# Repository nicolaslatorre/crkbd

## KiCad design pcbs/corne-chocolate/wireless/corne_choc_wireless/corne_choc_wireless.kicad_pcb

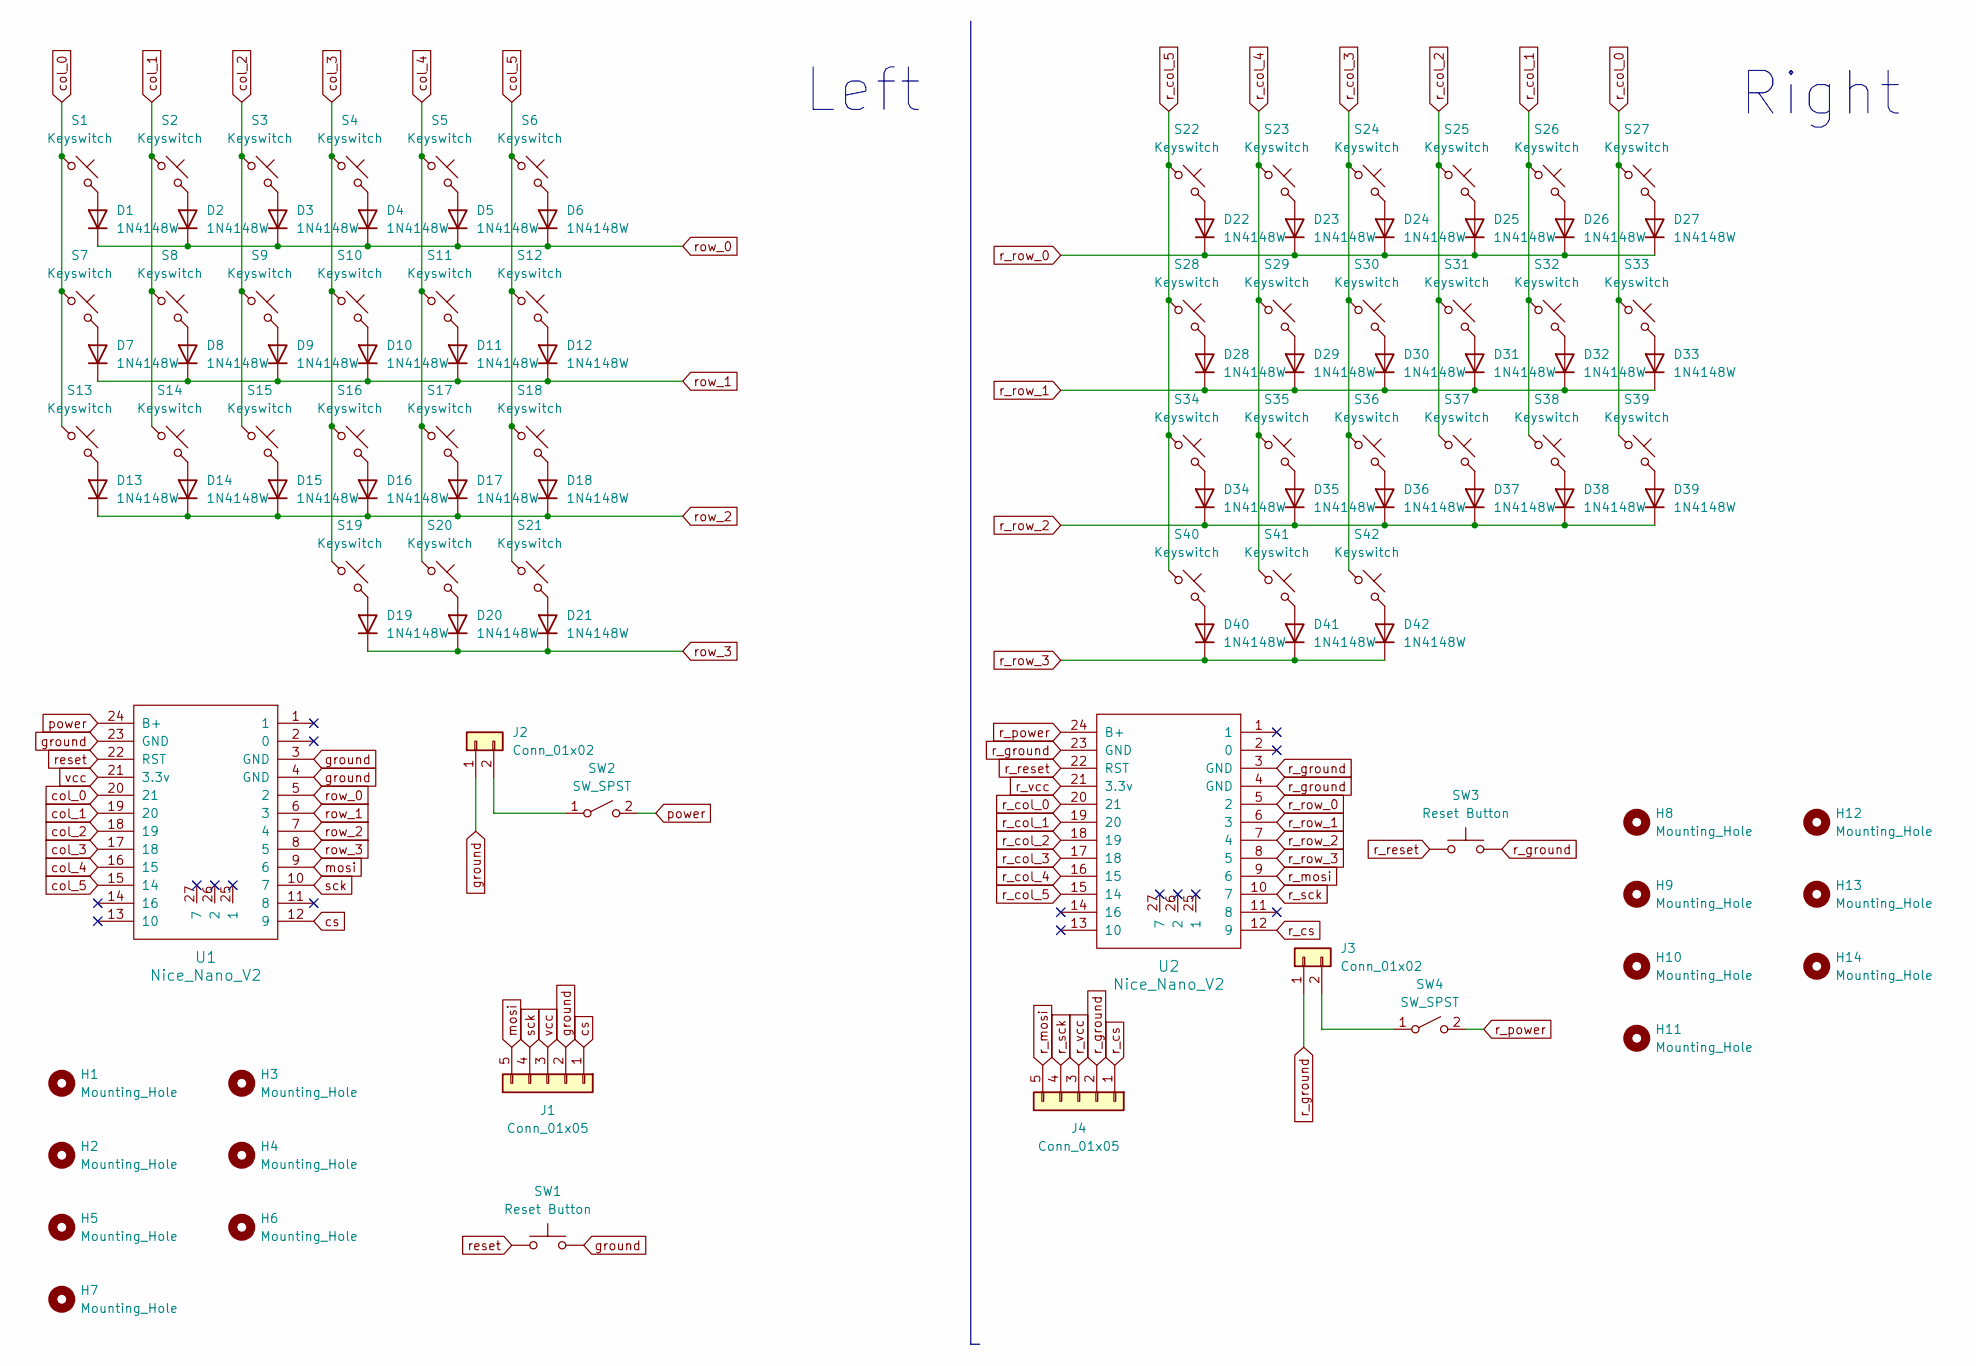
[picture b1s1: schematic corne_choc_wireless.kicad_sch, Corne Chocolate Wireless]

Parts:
D1, D2, D3, D4, D5, D6, D7, D8, D9, D10, D11, D12, D13, D14, D15, D16, D17, D18, D19, D20, D21, D22, D23, D24, D25, D26, D27, D28, D29, D30, D31, D32, D33, D34, D35, D36, D37, D38, D39, D40, D41, D42: 1N4148W; D_SOD-123
H1, H2, H3, H4, H5, H6, H7, H8, H9, H10, H11, H12, H13, H14: Mounting_Hole; MountingHole_2.2mm_M2_Pad
J1, J4: Conn_01x05; PinHeader_1x05_P2.54mm_Vertical
J2, J3: Conn_01x02; JST_PH_S2B-PH-K_1x02_P2.00mm_Horizontal
S1, S2, S3, S4, S5, S6, S7, S8, S9, S10, S11, S12, S13, S14, S15, S16, S17, S18, S19, S20, S22, S23, S24, S25, S26, S27, S28, S29, S30, S31, S32, S33, S34, S35, S36, S37, S38, S39, S41, S42: Keyswitch; Hotswap_Choc_V1_1.00u
S21, S40: Keyswitch; Hotswap_Choc_V1_1.50u
SW1, SW3: Reset Button; Button_MJTP1243
SW2, SW4: SW_SPST; Switch_MSK12C02
U1, U2: Nice_Nano_V2

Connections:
unnamed: D1.2 (A), S1.2
unnamed: D2.2 (A), S2.2
unnamed: D3.2 (A), S3.2
unnamed: D4.2 (A), S4.2
unnamed: D5.2 (A), S5.2
unnamed: D6.2 (A), S6.2
unnamed: D7.2 (A), S7.2
unnamed: D8.2 (A), S8.2
unnamed: D9.2 (A), S9.2
unnamed: D10.2 (A), S10.2
unnamed: D11.2 (A), S11.2
unnamed: D12.2 (A), S12.2
unnamed: D13.2 (A), S13.2
unnamed: D14.2 (A), S14.2
unnamed: D15.2 (A), S15.2
unnamed: D16.2 (A), S16.2
unnamed: D17.2 (A), S17.2
unnamed: D18.2 (A), S18.2
unnamed: D19.2 (A), S19.2
unnamed: D20.2 (A), S20.2
unnamed: D21.2 (A), S21.2
unnamed: D22.2 (A), S22.2
unnamed: D23.2 (A), S23.2
unnamed: D24.2 (A), S24.2
unnamed: D25.2 (A), S25.2
unnamed: D26.2 (A), S26.2
unnamed: D27.2 (A), S27.2
unnamed: D28.2 (A), S28.2
unnamed: D29.2 (A), S29.2
unnamed: D30.2 (A), S30.2
unnamed: D31.2 (A), S31.2
unnamed: D32.2 (A), S32.2
unnamed: D33.2 (A), S33.2
unnamed: D34.2 (A), S34.2
unnamed: D35.2 (A), S35.2
unnamed: D36.2 (A), S36.2
unnamed: D37.2 (A), S37.2
unnamed: D38.2 (A), S38.2
unnamed: D39.2 (A), S39.2
unnamed: D40.2 (A), S40.2
unnamed: D41.2 (A), S41.2
unnamed: D42.2 (A), S42.2
unnamed: J2.2, SW2.1 (A)
unnamed: J3.2, SW4.1 (A)
col_0: S1.1, S7.1, S13.1, U1.20 (21)
col_1: S2.1, S8.1, S14.1, U1.19 (20)
col_2: S3.1, S9.1, S15.1, U1.18 (19)
col_3: S4.1, S10.1, S16.1, S19.1, U1.17 (18)
col_4: S5.1, S11.1, S17.1, S20.1, U1.16 (15)
col_5: S6.1, S12.1, S18.1, S21.1, U1.15 (14)
cs: J1.1, U1.12 (9)
ground: J1.2, J2.1, SW1.2, U1.3 (GND), U1.4 (GND), U1.23 (GND)
mosi: J1.5, U1.9 (6)
power: SW2.2 (B), U1.24 (B+)
r_col_0: S27.1, S33.1, S39.1, U2.20 (21)
r_col_1: S26.1, S32.1, S38.1, U2.19 (20)
r_col_2: S25.1, S31.1, S37.1, U2.18 (19)
r_col_3: S24.1, S30.1, S36.1, S42.1, U2.17 (18)
r_col_4: S23.1, S29.1, S35.1, S41.1, U2.16 (15)
r_col_5: S22.1, S28.1, S34.1, S40.1, U2.15 (14)
r_cs: J4.1, U2.12 (9)
r_ground: J3.1, J4.2, SW3.2, U2.3 (GND), U2.4 (GND), U2.23 (GND)
r_mosi: J4.5, U2.9 (6)
r_power: SW4.2 (B), U2.24 (B+)
r_reset: SW3.1, U2.22 (RST)
r_row_0: D22.1 (K), D23.1 (K), D24.1 (K), D25.1 (K), D26.1 (K), D27.1 (K), U2.5 (2)
r_row_1: D28.1 (K), D29.1 (K), D30.1 (K), D31.1 (K), D32.1 (K), D33.1 (K), U2.6 (3)
r_row_2: D34.1 (K), D35.1 (K), D36.1 (K), D37.1 (K), D38.1 (K), D39.1 (K), U2.7 (4)
r_row_3: D40.1 (K), D41.1 (K), D42.1 (K), U2.8 (5)
r_sck: J4.4, U2.10 (7)
r_vcc: J4.3, U2.21 (3.3v)
reset: SW1.1, U1.22 (RST)
row_0: D1.1 (K), D2.1 (K), D3.1 (K), D4.1 (K), D5.1 (K), D6.1 (K), U1.5 (2)
row_1: D7.1 (K), D8.1 (K), D9.1 (K), D10.1 (K), D11.1 (K), D12.1 (K), U1.6 (3)
row_2: D13.1 (K), D14.1 (K), D15.1 (K), D16.1 (K), D17.1 (K), D18.1 (K), U1.7 (4)
row_3: D19.1 (K), D20.1 (K), D21.1 (K), U1.8 (5)
sck: J1.4, U1.10 (7)
vcc: J1.3, U1.21 (3.3v)

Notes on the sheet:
Right
Left

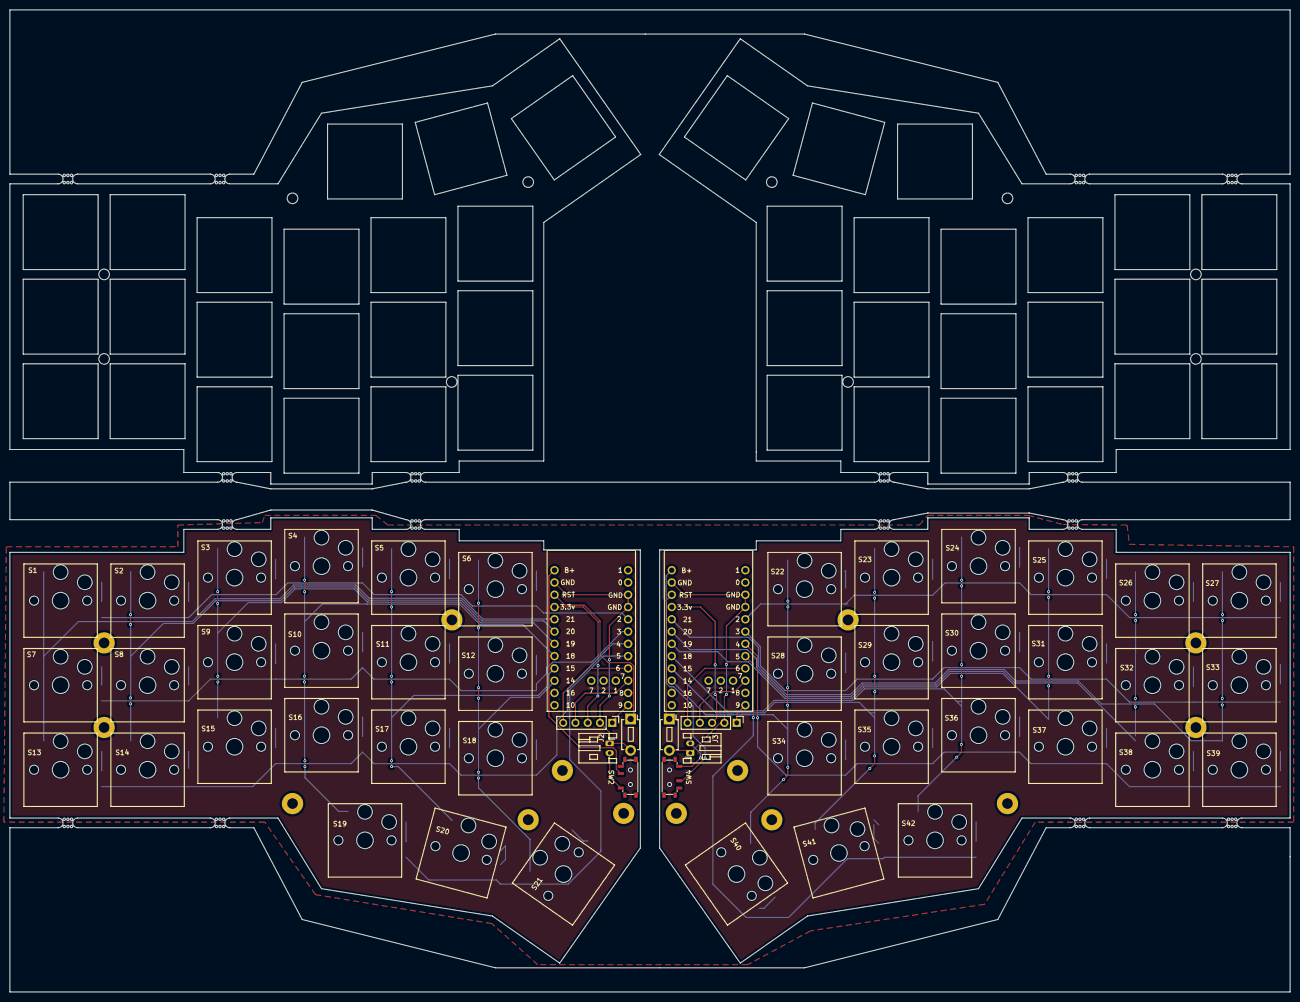
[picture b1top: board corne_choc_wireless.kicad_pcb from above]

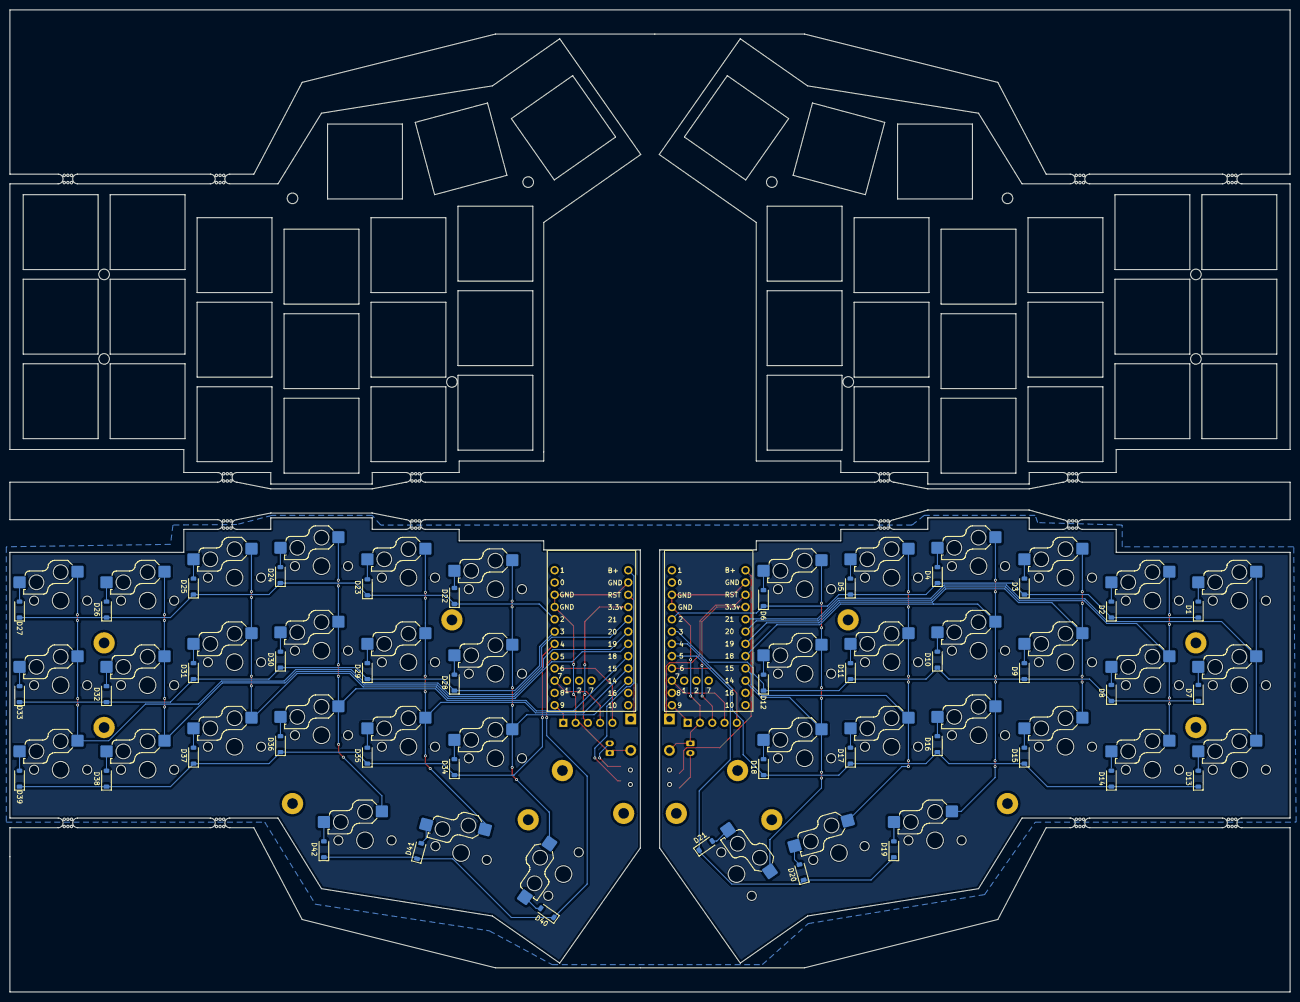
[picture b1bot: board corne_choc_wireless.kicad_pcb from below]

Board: 2 copper layers, 265.0 x 203.3 mm, 108 parts (44 on the bottom side), 78 nets.

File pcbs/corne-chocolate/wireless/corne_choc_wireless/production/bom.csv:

Designator,Footprint,Quantity,Value,LCSC Part #
"D1, D10, D11, D12, D13, D14, D15, D16, D17, D18, D19, D2, D20, D21, D22, D23, D24, D25, D26, D27, D28, D29, D3, D30, D31, D32, D33, D34, D35, D36, D37, D38, D39, D4, D40, D41, D42, D5, D6, D7, D8, D9",D_SOD-123,42,1N4148W,
"H1, H10, H11, H12, H13, H14, H2, H3, H4, H5, H6, H7, H8, H9",MountingHole_2.2mm_M2_Pad,14,Mounting_Hole,
"J1, J4",PinHeader_1x05_P2.54mm_Vertical,2,Conn_01x05,
"J2, J3",JST_PH_S2B-PH-K_1x02_P2.00mm_Horizontal,2,Conn_01x02,
"S1, S10, S11, S12, S13, S14, S15, S16, S17, S18, S19, S2, S20, S22, S23, S24, S25, S26, S27, S28, S29, S3, S30, S31, S32, S33, S34, S35, S36, S37, S38, S39, S4, S41, S42, S5, S6, S7, S8, S9",Hotswap_Choc_V1_1.00u,40,Keyswitch,
"S21, S40",Hotswap_Choc_V1_1.50u,2,Keyswitch,
"SW1, SW3",Button_MJTP1243,2,Reset Button,
"SW2, SW4",Switch_MSK12C02,2,SW_SPST,
"U1, U2",Nice_Nano_V2,2,Nice_Nano_V2,

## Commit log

2024-11-26 finished routing pcb
2025-03-28 Gerber file V1
    Gerber file V1
2025-04-02 Gerber file V2
    Gerber file V2
